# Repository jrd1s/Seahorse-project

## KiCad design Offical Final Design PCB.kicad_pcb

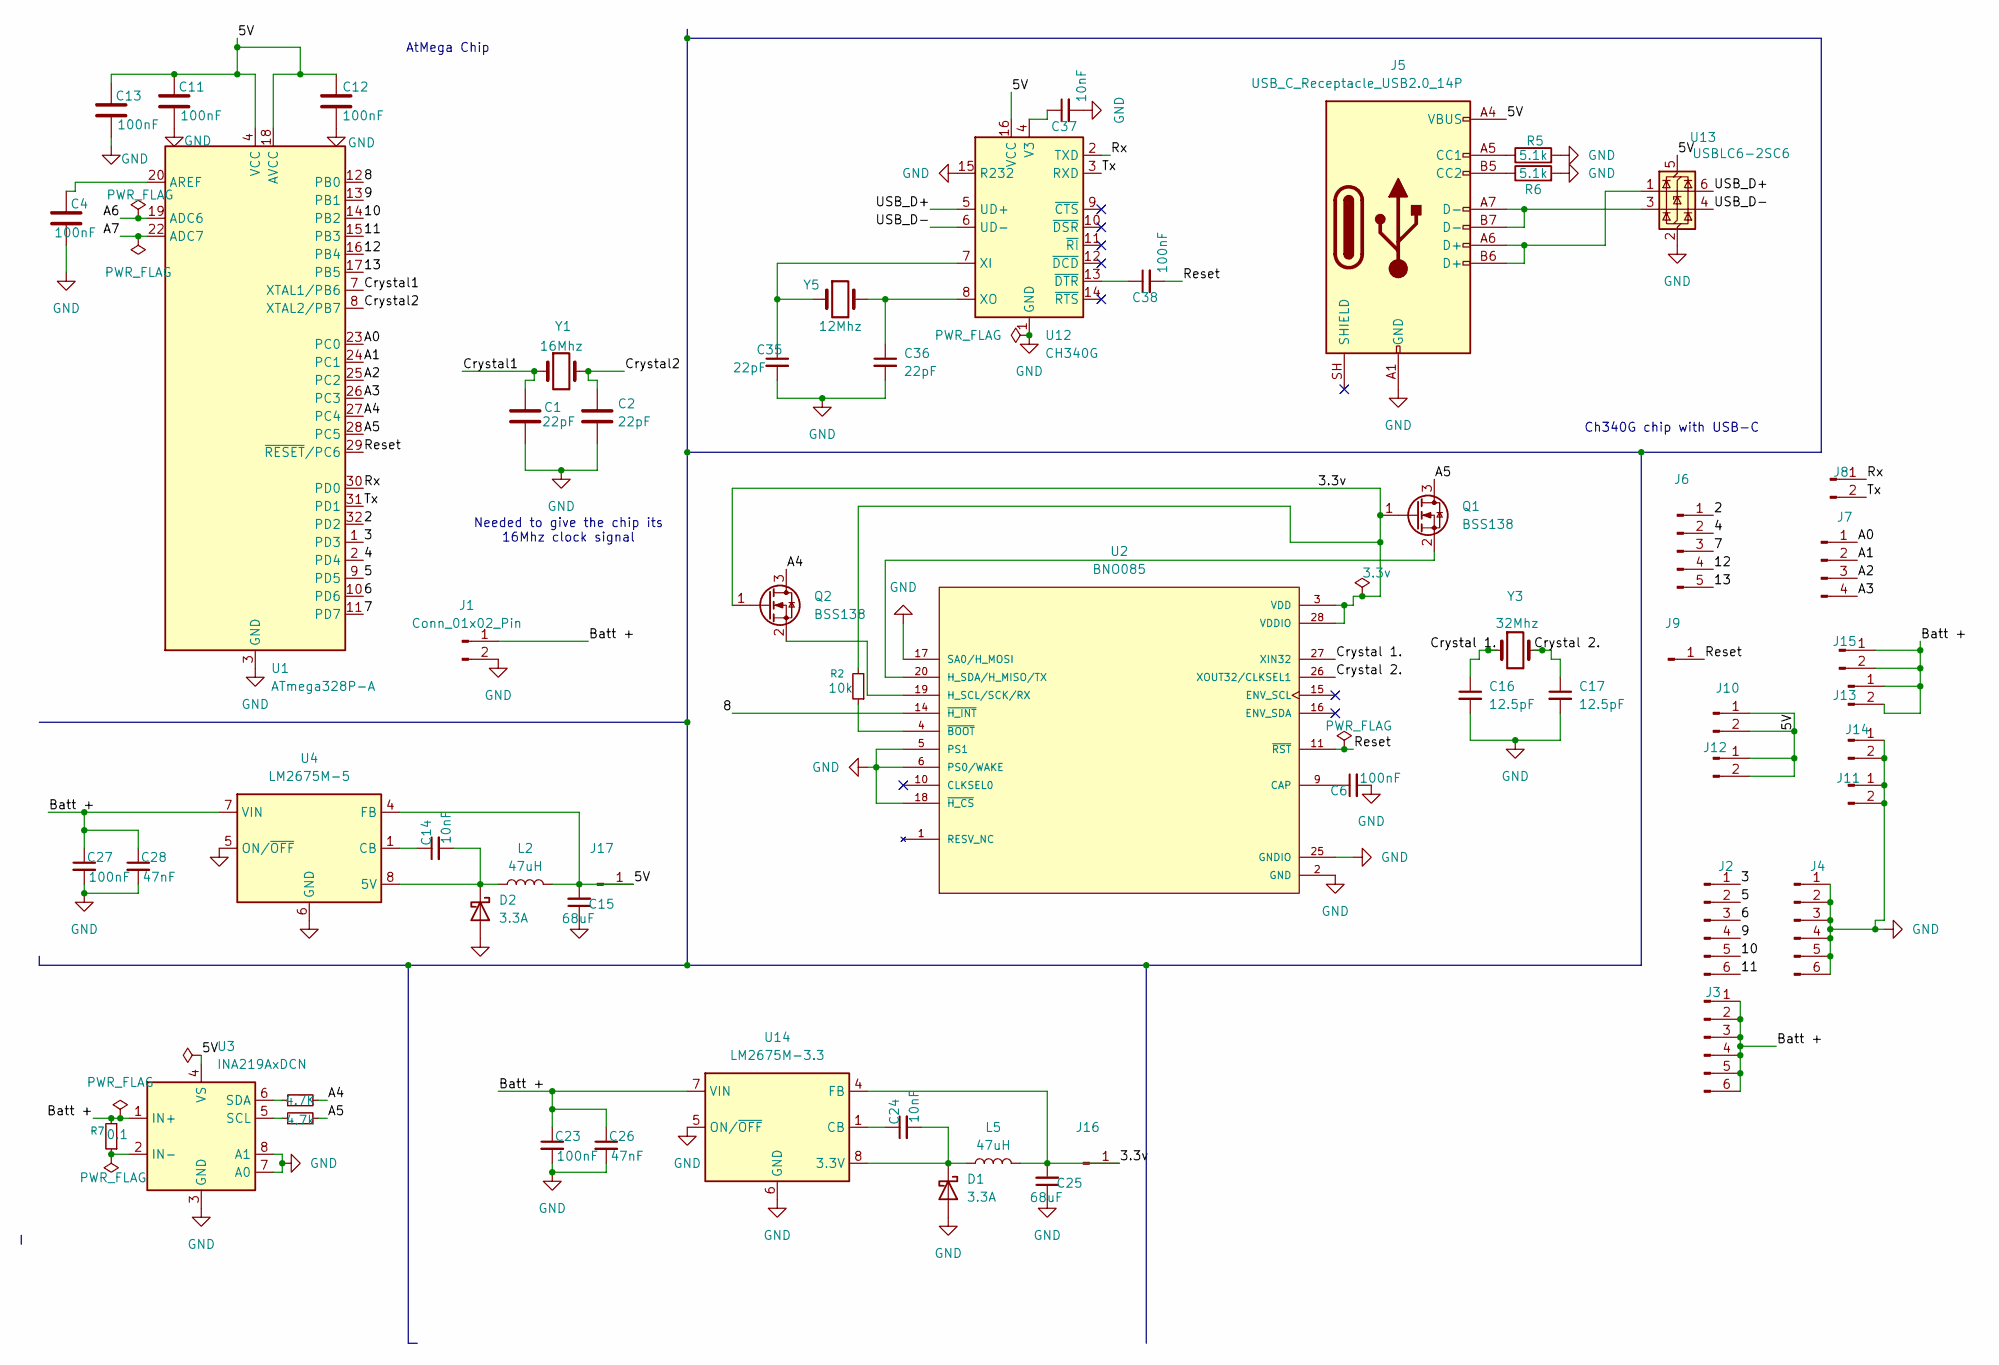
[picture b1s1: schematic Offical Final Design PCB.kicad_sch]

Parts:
C1, C2, C35, C36: 22pF; C_0603_1608Metric_Pad1.08x0.95mm_HandSolder
C4, C6, C11, C12, C13, C23, C27, C38: 100nF; C_0603_1608Metric_Pad1.08x0.95mm_HandSolder
C14, C24, C37: 10nF; C_0603_1608Metric_Pad1.08x0.95mm_HandSolder
C15, C25: 68uF; C_0603_1608Metric_Pad1.08x0.95mm_HandSolder
C16, C17: 12.5pF; C_0603_1608Metric_Pad1.08x0.95mm_HandSolder
C26, C28: 47nF; C_0603_1608Metric_Pad1.08x0.95mm_HandSolder
D1, D2: 3.3A; D_SOD-523
J1, J8, J10, J11, J12, J13, J14, J15: Conn_01x02_Pin; PinHeader_1x02_P2.54mm_Vertical
J2, J3, J4: Conn_01x06_Pin; PinHeader_1x06_P2.54mm_Vertical
J5: USB_C_Receptacle_USB2.0_14P; USB_C_Receptacle_GCT_USB4105-xx-A_16P_TopMnt_Horizontal
J6: Conn_01x05_Pin; PinHeader_1x05_P2.54mm_Vertical
J7: Conn_01x04_Pin; PinHeader_1x04_P2.54mm_Vertical
J9, J16, J17: Conn_01x01_Pin; PinHeader_1x01_P2.54mm_Vertical
L2, L5: 47uH; L_01005_0402Metric_Pad0.57x0.30mm_HandSolder
Q1, Q2: BSS138; SOT-23
R2: 10k; R_0603_1608Metric_Pad0.98x0.95mm_HandSolder
R3: 4.7K; R_0603_1608Metric_Pad0.98x0.95mm_HandSolder
R4: 4.7k; R_0603_1608Metric_Pad0.98x0.95mm_HandSolder
R5, R6: 5.1k; R_0603_1608Metric_Pad0.98x0.95mm_HandSolder
R7: 0.1; R_0603_1608Metric_Pad0.98x0.95mm_HandSolder
U1: ATmega328P-A; TQFP-32_7x7mm_P0.8mm
U2: BNO085; IC_BNO085; PARTREV v1.17
U3: INA219AxDCN; SOT-23-8
U4: LM2675M-5; SOIC-8_3.9x4.9mm_P1.27mm
U12: CH340G; SOIC-16_3.9x9.9mm_P1.27mm
U13: USBLC6-2SC6; SOT-23-6
U14: LM2675M-3.3; SOIC-8_3.9x4.9mm_P1.27mm
Y1: 16Mhz; Crystal_DS10_D1.0mm_L4.3mm_Horizontal
Y3: 32Mhz; Crystal_DS10_D1.0mm_L4.3mm_Horizontal
Y5: 12Mhz; Crystal_DS10_D1.0mm_L4.3mm_Horizontal

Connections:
/2: J6.1, U1.32 (PD2)
/3: J2.1, U1.1 (PD3)
/3.3v: C25.2, J16.1, L5.2, Q1.1 (G), Q2.1 (G), R2.2, U2.3 (VDD), U2.28 (VDDIO), U14.4 (FB)
/4: J6.2, U1.2 (PD4)
/5: J2.2, U1.9 (PD5)
/5V: C11.1, C12.1, C13.1, C15.2, J5.A4 (VBUS), J5.A9 (VBUS), J5.B4 (VBUS), J5.B9 (VBUS), J10.1, J10.2, J12.1, J12.2, J17.1, L2.2, U1.4 (VCC), U1.6 (VCC), U1.18 (AVCC), U3.4 (VS), U4.4 (FB), U12.16 (VCC), U13.5 (VBUS)
/6: J2.3, U1.10 (PD6)
/7: J6.3, U1.11 (PD7)
/8: U1.12 (PB0), U2.14 (~H_INT)
/9: J2.4, U1.13 (PB1)
/10: J2.5, U1.14 (PB2)
/11: J2.6, U1.15 (PB3)
/12: J6.4, U1.16 (PB4)
/13: J6.5, U1.17 (PB5)
/A0: J7.1, U1.23 (PC0)
/A1: J7.2, U1.24 (PC1)
/A2: J7.3, U1.25 (PC2)
/A3: J7.4, U1.26 (PC3)
/A4: Q2.3 (D), R3.2, U1.27 (PC4)
/A5: Q1.3 (D), R4.2, U1.28 (PC5)
/A6: U1.19 (ADC6)
/A7: U1.22 (ADC7)
/Batt +: C23.1, C26.1, C27.1, C28.1, J1.1, J3.1, J3.2, J3.3, J3.4, J3.5, J3.6, J13.1, J13.2, J15.1, J15.2, R7.2, U3.1 (IN+), U4.7 (VIN), U14.7 (VIN)
/Crystal1: C1.1, U1.7 (XTAL1/PB6), Y1.1
/Crystal2: C2.1, U1.8 (XTAL2/PB7), Y1.2
/Crystal 1.: C16.1, U2.27 (XIN32), Y3.1
/Crystal 2.: C17.1, U2.26 (XOUT32/CLKSEL1), Y3.2
/Reset: C38.2, J9.1 (Pin_1_1), U1.29 (~RESET/PC6), U2.11 (~RST)
/Rx: J8.1, U1.30 (PD0), U12.2 (TXD)
/Tx: J8.2, U1.31 (PD1), U12.3 (RXD)
/USB_D+: U12.5 (UD+), U13.6 (I/O1)
/USB_D-: U12.6 (UD-), U13.4 (I/O2)
GND: C1.2, C2.2, C4.2, C6.2, C11.2, C12.2, C13.2, C15.1, C16.2, C17.2, C23.2, C25.1, C26.2, C27.2, C28.2, C35.2, C36.2, C37.2, D1.2 (A), D2.2 (A), J1.2, J4.1, J4.2, J4.3, J4.4, J4.5, J4.6, J5.A1 (GND), J5.A12 (GND), J5.B1 (GND), J5.B12 (GND), J11.1, J11.2, J14.1, J14.2, R5.2, R6.2, U1.3 (GND), U1.5 (GND), U1.21 (GND), U2.2 (GND), U2.5 (PS1), U2.6 (PS0/WAKE), U2.17 (SA0/H_MOSI), U2.18 (~H_CS), U2.25 (GNDIO), U3.3 (GND), U3.7 (A0), U3.8 (A1), U4.5 (ON/~OFF), U4.6 (GND), U12.1 (GND), U12.15 (R232), U13.2 (GND), U14.5 (ON/~OFF), U14.6 (GND)
unnamed: C24.2, D1.1 (K), L5.1, U14.8 (3.3V)
unnamed: C14.2, D2.1 (K), L2.1, U4.8 (5V)
unnamed: J5.A5 (CC1), R5.1
unnamed: J5.B5 (CC2), R6.1
unnamed: J5.A6 (D+), J5.B6 (D+), U13.1 (I/O1)
unnamed: J5.A7 (D-), J5.B7 (D-), U13.3 (I/O2)
unnamed: Q1.2 (S), U2.20 (H_SDA/H_MISO/TX)
unnamed: Q2.2 (S), U2.19 (H_SCL/SCK/RX)
unnamed: C4.1, U1.20 (AREF)
unnamed: C6.1, U2.9 (CAP)
unnamed: R2.1, U2.4 (~BOOT)
unnamed: R7.1, U3.2 (IN-)
unnamed: R4.1, U3.5 (SCL)
unnamed: R3.1, U3.6 (SDA)
unnamed: C14.1, U4.1 (CB)
unnamed: C37.1, U12.4 (V3)
unnamed: C35.1, U12.7 (XI), Y5.1
unnamed: C36.1, U12.8 (XO), Y5.2
unnamed: C38.1, U12.13 (~DTR)
unnamed: C24.1, U14.1 (CB)

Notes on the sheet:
Needed to give the chip its 16Mhz clock signal
Ch340G chip with USB-C
AtMega Chip

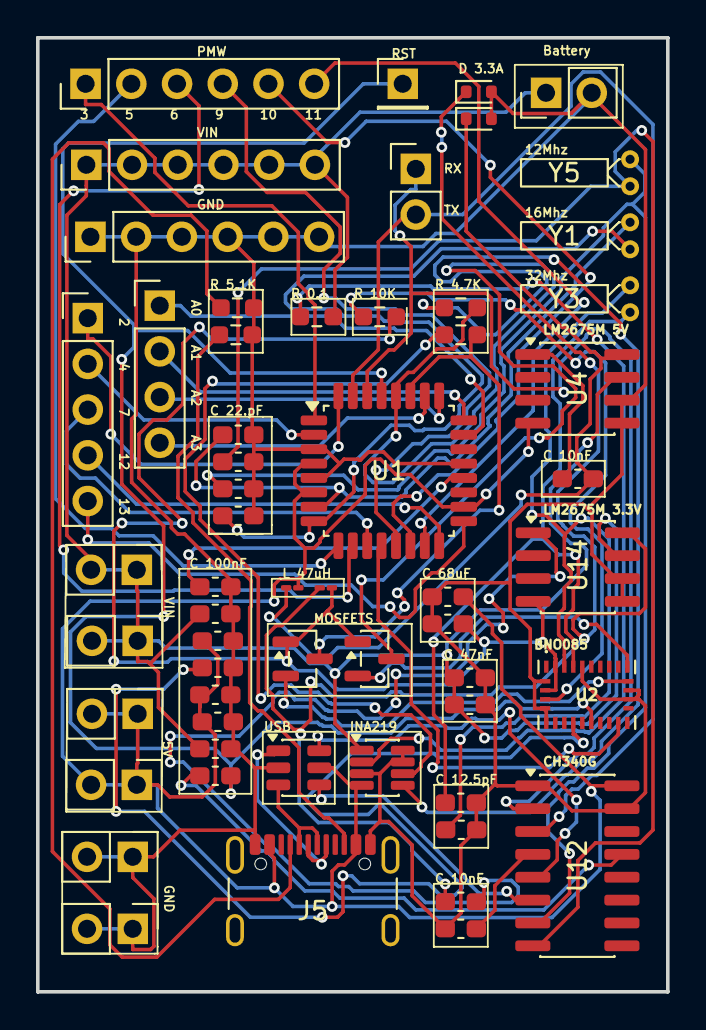
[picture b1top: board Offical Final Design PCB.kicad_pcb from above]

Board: 2 copper layers, 35.0 x 53.0 mm, 58 parts (0 on the bottom side), 51 nets.

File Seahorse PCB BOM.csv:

"Id";"Designator";"Footprint";"Quantity";"Designation";"Supplier and ref";
1;"C1, C2, C35, C36";"C_0603_1608Metric_Pad1.08x0.95mm_HandSolder";4;"22pF";;;
2;"C4, C6, C11, C12, C13, C23, C27, C38";"C_0603_1608Metric_Pad1.08x0.95mm_HandSolder";8;"100nF";;;
3;"C14, C24, C37";"C_0603_1608Metric_Pad1.08x0.95mm_HandSolder";3;"10nF";;;
4;"C15, C25";"C_0603_1608Metric_Pad1.08x0.95mm_HandSolder";2;"68uF";;;
5;"C16, C17";"C_0603_1608Metric_Pad1.08x0.95mm_HandSolder";2;"12.5pF";;;
6;"C26, C28";"C_0603_1608Metric_Pad1.08x0.95mm_HandSolder";2;"47nF";;;
7;"D1, D2";"D_SOD-523";2;"3.3A";;;
8;"J1, J8, J10, J11, J12, J13, J14, J15";"PinHeader_1x02_P2.54mm_Vertical";8;"Conn_01x02_Pin";;;
9;"J2, J3, J4";"PinHeader_1x06_P2.54mm_Vertical";3;"Conn_01x06_Pin";;;
10;"J5";"USB_C_Receptacle_GCT_USB4105-xx-A_16P_TopMnt_Horizontal";1;"USB_C_Receptacle_USB2.0_14P";;;
11;"J6";"PinHeader_1x05_P2.54mm_Vertical";1;"Conn_01x05_Pin";;;
12;"J7";"PinHeader_1x04_P2.54mm_Vertical";1;"Conn_01x04_Pin";;;
13;"J9";"PinHeader_1x01_P2.54mm_Vertical";1;"Conn_01x01_Pin";;;
14;"L2, L5";"L_01005_0402Metric_Pad0.57x0.30mm_HandSolder";2;"47uH";;;
15;"Q1, Q2";"SOT-23";2;"BSS138";;;
16;"R2";"R_0603_1608Metric_Pad0.98x0.95mm_HandSolder";1;"10k";;;
17;"R3";"R_0603_1608Metric_Pad0.98x0.95mm_HandSolder";1;"4.7K";;;
18;"R4";"R_0603_1608Metric_Pad0.98x0.95mm_HandSolder";1;"4.7k";;;
19;"R5, R6";"R_0603_1608Metric_Pad0.98x0.95mm_HandSolder";2;"5.1k";;;
20;"R7";"R_0603_1608Metric_Pad0.98x0.95mm_HandSolder";1;"0.1";;;
21;"U1";"TQFP-32_7x7mm_P0.8mm";1;"ATmega328P-A";;;
22;"U2";"IC_BNO085";1;"BNO085";;;
23;"U3";"SOT-23-8";1;"INA219AxDCN";;;
24;"U4";"SOIC-8_3.9x4.9mm_P1.27mm";1;"LM2675M-5";;;
25;"U12";"SOIC-16_3.9x9.9mm_P1.27mm";1;"CH340G";;;
26;"U13";"SOT-23-6";1;"USBLC6-2SC6";;;
27;"U14";"SOIC-8_3.9x4.9mm_P1.27mm";1;"LM2675M-3.3";;;
28;"Y1";"Crystal_DS10_D1.0mm_L4.3mm_Horizontal";1;"16Mhz";;;
29;"Y3";"Crystal_DS10_D1.0mm_L4.3mm_Horizontal";1;"32Mhz";;;
30;"Y5";"Crystal_DS10_D1.0mm_L4.3mm_Horizontal";1;"12Mhz";;;
